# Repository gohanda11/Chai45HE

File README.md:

# Chai45HE

Chai45HE is a 40% Hall-effect keyboard based on the [HE60](https://github.com/peppapighs/HE60) project. This is a modified version that adapts the original 60% design to a compact 40% layout.

## Key Features

- 40% compact layout
- Hall-effect magnetic switches support
- Based on HE60's proven design and technology
- Custom PCB design files included

## ファームウェアの書き込み方法

1. [firmware.bin](firmware/firmware.bin) をダウンロードします。
2. 基板裏側の **BOOT** ボタンを長押ししながらUSBケーブルを接続し、Bootloader Modeに入ります。
3. [WebDFU](https://devanlai.github.io/webdfu/dfu-util/) にアクセスし、**DFU in FS mode** に接続します。
4. **Firmware Download** セクションでダウンロードした `firmware.bin` ファイルを選択します。
5. **Download** ボタンを押して書き込みを実行します。

## キー設定ガイド

### Tap-Holdの設定方法

Tap-Holdを使うと、短押し(Tap)と長押し(Hold)で異なるキーを割り当てることができます。

1. Remapで **Tap** に設定したいキーを配置します。
2. **Advanced Keys** から **Tap-Hold** を選択します。
3. **Hold** に設定したいキーを選択し、**Continue** を押します。
4. Hold用のキーを設定して **Done** で設定完了です。

### !@#$%などの記号キーの設定方法

Shiftキーとの組み合わせで入力される記号(!@#$%など)を単独のキーとして設定する方法です。

1. Remapで `1 2 3 4 5` を、`! @ # $ %` を入力したいキーに設定します。
2. **Advanced Keys** から **Dynamic Keystroke** を選択します。
3. 下の画像のようにShiftを割り当てます。

4. **Done** で設定完了です。

---

# HE60 (Original Project)

Below is the original README from the HE60 project, which this keyboard is based on.

---

# HE60

HE60 is a 60% Hall-effect keyboard PCB with 8kHz polling rate, a split spacebar and Tsangan layout support.

## Features

- Support for GH60 tray mount cases e.g., KBDfans Tofu60 Redux, and KBDfans Holy60.
- Support for gummy O-ring mount cases **if the USB-C port is not soldered** e.g., Bakeneko60, and SingaKBD Unikorn (required 10mm JST cable).
- [libhmk](https://github.com/peppapighs/libhmk) firmware.
- [hmkconf](https://hmk.prasertsuk.com) web-based configurator.

## Disclaimer

- The PCB requires standoffs to be mounted to the switch plate. The mounting points are **not compatible** with other available plates e.g., GEON Venom60 7U plate. HE60 v1 plate **is not compatible** with this PCB.

## Supported Layouts

## Fabrication

The following files are required:

- BOM (Bill of Materials): Contains the list of components required to build the PCB.
- Pick and Place: Contains the placement of the components on the PCB.
- Gerber: Contains the PCB design files for fabrication.

Note that the components in the BOM are all mounted on the bottom side of the PCB, and are based on the available components in JLCPCB at the time of writing. You may need to adjust the components based on your preference or availability. For the JST connector (labeled `JST_SH`), I used `WAFER-SH1.0-4PWB` offered by JLCPCB. **Make sure to deselect the USB-C port when choosing the components to solder if you are using the gummy O-ring version.**

You may change the Hall-effect sensors during the component selection based on your preference, and availability. Different sensors require different calibration values, which can be adjusted using the web-based configurator. Here are some options that I have used:

- GH39FKSW (Cheapest)
- MT9102ET
- SS39ET
- DRV5055A3
- OH49E-S (Discontinued)

The fabrication files above are available [here](https://github.com/peppapighs/HE60/releases).

## Build Guide

The following items are required to build the PCB:

- PCB
- Switch plate (DXF file available [here](/plate.dxf). You may need to use less flexible materials such as aluminum or FR4 to prevent the switch at the top right corner from popping out if you use the alternative backspace layout. If you would like to manufacture FR4 plate along with the PCB, you can find the GERBER file for the plate [here](https://github.com/peppapighs/HE60/releases).)
- Magnetic switches (e.g., GEON Raw HE, Gateron Magnetic Jade, Duhuk Core HE, etc.)
- Stabilizers (**Clip-in stabilizers are required for the gummy O-ring version**)
- M2 3.5mm standoffs x8
- M2 3mm flat head screws x16

1. Install the stabilizers to the PCB.

2. Attach the standoffs to the PCB using the M2 screws.

3. Install the switches to the plate. Assemble the plate and PCB together. Press the PCB against the plate to make sure the switches are seated properly. Screw the standoffs to the plate using the rest of the M2 screws.

4. Install the PCB into the case.

## Firmware

Head to [libhmk](https://github.com/peppapighs/libhmk/releases) for a pre-compiled firmware. The firmware can be flashed using DFU mode, which can be entered by holding the BOOT button before plugging in. You may need to install the DFU bootloader driver using Zadig. See [libhmk](https://github.com/peppapighs/libhmk) for more information for firmware flashing instructions.

## Acknowledgements

- Xelus from AEBoards for reviewing the PCB design and providing feedback.
- Keyboard Atelier community for supporting the project.

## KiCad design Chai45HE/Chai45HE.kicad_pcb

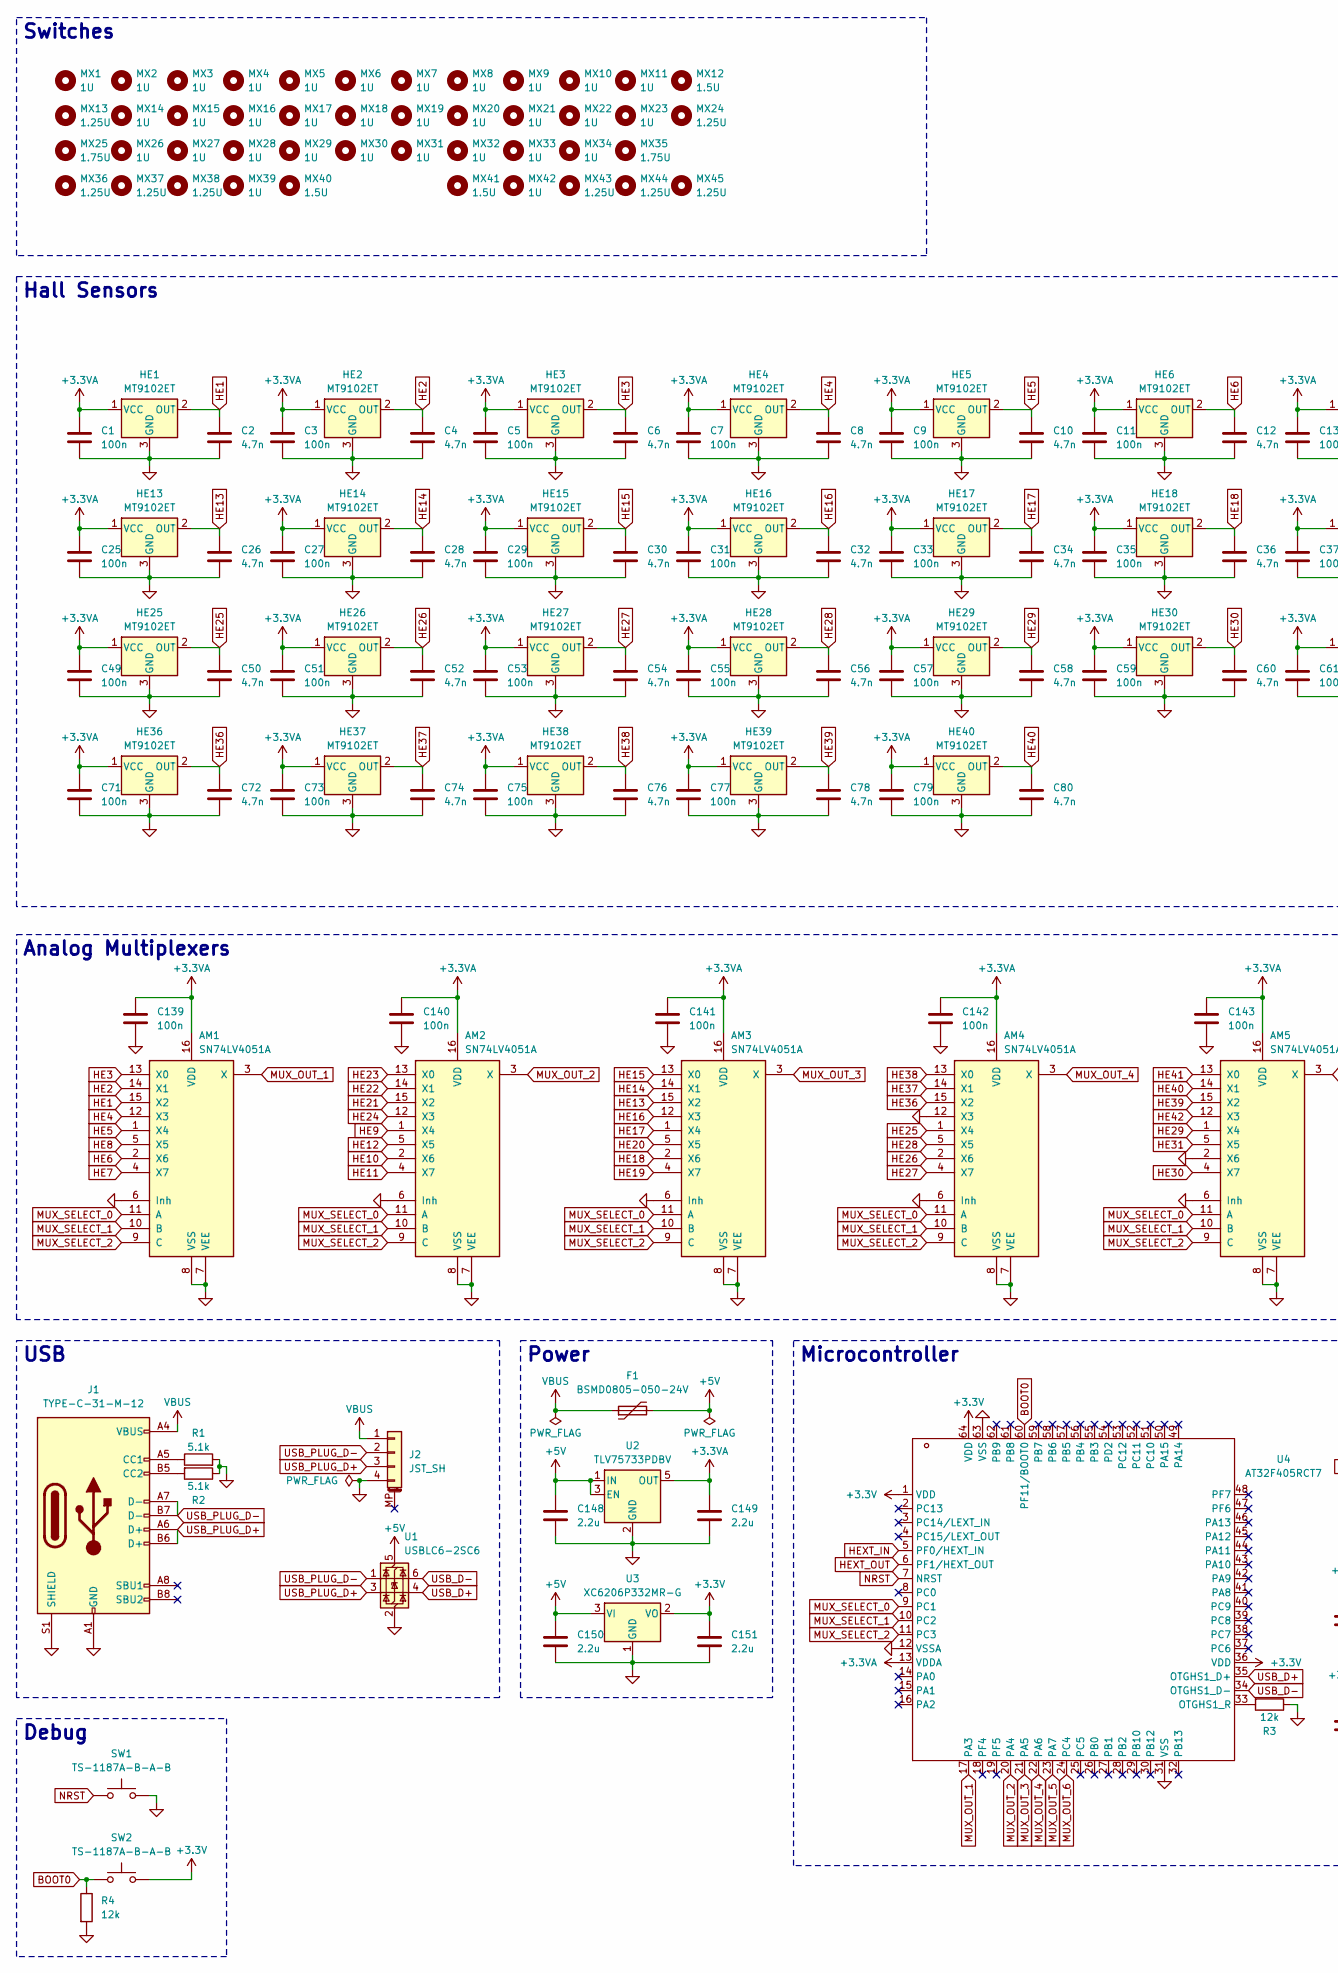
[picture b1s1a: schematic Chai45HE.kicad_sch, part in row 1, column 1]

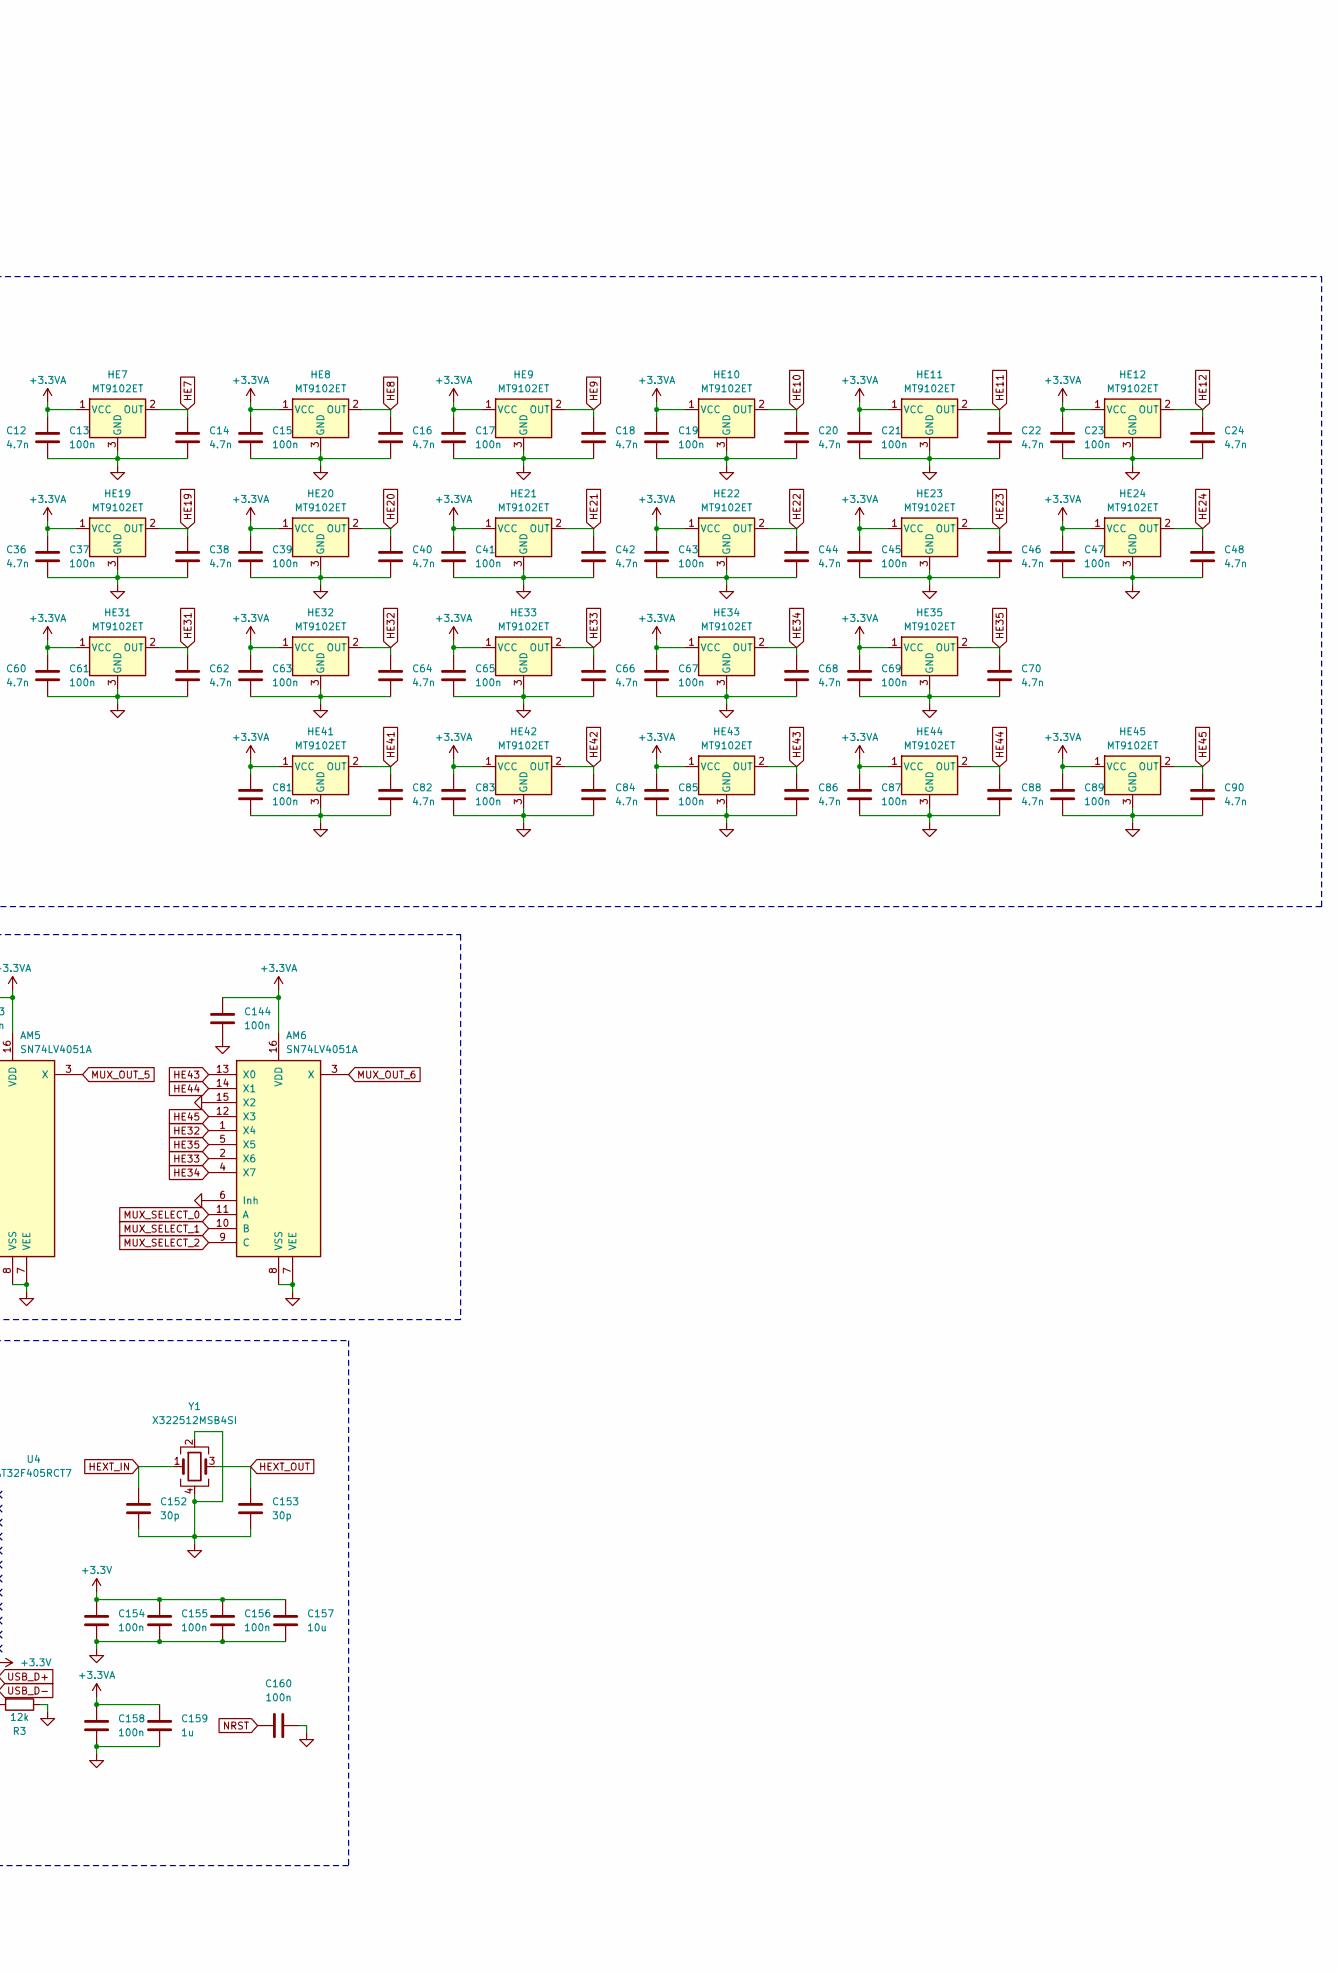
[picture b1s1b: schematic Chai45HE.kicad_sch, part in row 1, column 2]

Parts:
AM1, AM2, AM3, AM4, AM5, AM6: SN74LV4051A; TSSOP-16_4.4x5mm_P0.65mm
C1, C3, C5, C7, C9, C11, C13, C15, C17, C19, C21, C23, C25, C27, C29, C31, C33, C35, C37, C39, C41, C43, C45, C47, C49, C51, C53, C55, C57, C59, C61, C63, C65, C67, C69, C71, C73, C75, C77, C79, C81, C83, C85, C87, C89, C139, C140, C141, C142, C143, C144, C154, C155, C156, C158, C160: 100n; C_0402_1005Metric
C2, C4, C6, C8, C10, C12, C14, C16, C18, C20, C22, C24, C26, C28, C30, C32, C34, C36, C38, C40, C42, C44, C46, C48, C50, C52, C54, C56, C58, C60, C62, C64, C66, C68, C70, C72, C74, C76, C78, C80, C82, C84, C86, C88, C90: 4.7n; C_0402_1005Metric
C148, C149, C150, C151: 2.2u; C_0603_1608Metric
C152, C153: 30p; C_0603_1608Metric
C157: 10u; C_0603_1608Metric
C159: 1u; C_0603_1608Metric
F1: BSMD0805-050-24V; Fuse_0805_2012Metric
HE1, HE2, HE3, HE4, HE5, HE6, HE7, HE8, HE9, HE10, HE11, HE12, HE13, HE14, HE15, HE16, HE17, HE18, HE19, HE20, HE21, HE22, HE23, HE24, HE25, HE26, HE27, HE28, HE29, HE30, HE31, HE32, HE33, HE34, HE35, HE36, HE37, HE38, HE39, HE40, HE41, HE42, HE43, HE44, HE45: MT9102ET; SOT-23-3
J1: TYPE-C-31-M-12; USB_C_Receptacle_HRO_TYPE-C-31-M-12
J2: JST_SH; JST_SH_SM04B-SRSS-TB_1x04-1MP_P1.00mm_Horizontal
MX1, MX2, MX3, MX4, MX5, MX6, MX7, MX8, MX9, MX10, MX11, MX14, MX15, MX16, MX17, MX18, MX19, MX20, MX21, MX22, MX23, MX26, MX27, MX28, MX29, MX30, MX31, MX32, MX33, MX34, MX39, MX42: 1U; MX-1U
MX12, MX40, MX41: 1.5U; MX-1.5U
MX13, MX24, MX36, MX37, MX38, MX43, MX44, MX45: 1.25U; MX-1.25U
MX25, MX35: 1.75U; MX-1.75U
R1, R2: 5.1k; R_0402_1005Metric
R3, R4: 12k; R_0402_1005Metric
SW1, SW2: TS-1187A-B-A-B; SW_Push_1P1T_XKB_TS-1187A
U1: USBLC6-2SC6; SOT-23-6
U2: TLV75733PDBV; SOT-23-5
U3: XC6206P332MR-G; SOT-23-3
U4: AT32F405RCT7; LQFP-64_10x10mm_P0.5mm
Y1: X322512MSB4SI; Crystal_SMD_3225-4Pin_3.2x2.5mm

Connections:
+3.3V: C151.1, C154.1, C155.1, C156.1, C157.1, SW2.2, U3.2 (VO), U4.1 (VDD), U4.36 (VDD), U4.64 (VDD)
+3.3VA: AM1.16 (VDD), AM2.16 (VDD), AM3.16 (VDD), AM4.16 (VDD), AM5.16 (VDD), AM6.16 (VDD), C1.1, C3.1, C5.1, C7.1, C9.1, C11.1, C13.1, C15.1, C17.1, C19.1, C21.1, C23.1, C25.1, C27.1, C29.1, C31.1, C33.1, C35.1, C37.1, C39.1, C41.1, C43.1, C45.1, C47.1, C49.1, C51.1, C53.1, C55.1, C57.1, C59.1, C61.1, C63.1, C65.1, C67.1, C69.1, C71.1, C73.1, C75.1, C77.1, C79.1, C81.1, C83.1, C85.1, C87.1, C89.1, C139.1, C140.1, C141.1, C142.1, C143.1, C144.1, C149.1, C158.1, C159.1, HE1.1 (VCC), HE2.1 (VCC), HE3.1 (VCC), HE4.1 (VCC), HE5.1 (VCC), HE6.1 (VCC), HE7.1 (VCC), HE8.1 (VCC), HE9.1 (VCC), HE10.1 (VCC), HE11.1 (VCC), HE12.1 (VCC), HE13.1 (VCC), HE14.1 (VCC), HE15.1 (VCC), HE16.1 (VCC), HE17.1 (VCC), HE18.1 (VCC), HE19.1 (VCC), HE20.1 (VCC), HE21.1 (VCC), HE22.1 (VCC), HE23.1 (VCC), HE24.1 (VCC), HE25.1 (VCC), HE26.1 (VCC), HE27.1 (VCC), HE28.1 (VCC), HE29.1 (VCC), HE30.1 (VCC), HE31.1 (VCC), HE32.1 (VCC), HE33.1 (VCC), HE34.1 (VCC), HE35.1 (VCC), HE36.1 (VCC), HE37.1 (VCC), HE38.1 (VCC), HE39.1 (VCC), HE40.1 (VCC), HE41.1 (VCC), HE42.1 (VCC), HE43.1 (VCC), HE44.1 (VCC), HE45.1 (VCC), U2.5 (OUT), U4.13 (VDDA)
+5V: C148.1, C150.1, F1.2, U1.5 (VBUS), U2.1 (IN), U2.3 (EN), U3.3 (VI)
BOOT0: R4.1, SW2.1, U4.60 (PF11/BOOT0)
GND: AM1.6 (Inh), AM1.7 (VEE), AM1.8 (VSS), AM2.6 (Inh), AM2.7 (VEE), AM2.8 (VSS), AM3.6 (Inh), AM3.7 (VEE), AM3.8 (VSS), AM4.6 (Inh), AM4.7 (VEE), AM4.8 (VSS), AM4.12 (X3), AM5.2 (X6), AM5.6 (Inh), AM5.7 (VEE), AM5.8 (VSS), AM6.6 (Inh), AM6.7 (VEE), AM6.8 (VSS), AM6.15 (X2), C1.2, C2.2, C3.2, C4.2, C5.2, C6.2, C7.2, C8.2, C9.2, C10.2, C11.2, C12.2, C13.2, C14.2, C15.2, C16.2, C17.2, C18.2, C19.2, C20.2, C21.2, C22.2, C23.2, C24.2, C25.2, C26.2, C27.2, C28.2, C29.2, C30.2, C31.2, C32.2, C33.2, C34.2, C35.2, C36.2, C37.2, C38.2, C39.2, C40.2, C41.2, C42.2, C43.2, C44.2, C45.2, C46.2, C47.2, C48.2, C49.2, C50.2, C51.2, C52.2, C53.2, C54.2, C55.2, C56.2, C57.2, C58.2, C59.2, C60.2, C61.2, C62.2, C63.2, C64.2, C65.2, C66.2, C67.2, C68.2, C69.2, C70.2, C71.2, C72.2, C73.2, C74.2, C75.2, C76.2, C77.2, C78.2, C79.2, C80.2, C81.2, C82.2, C83.2, C84.2, C85.2, C86.2, C87.2, C88.2, C89.2, C90.2, C139.2, C140.2, C141.2, C142.2, C143.2, C144.2, C148.2, C149.2, C150.2, C151.2, C152.2, C153.2, C154.2, C155.2, C156.2, C157.2, C158.2, C159.2, C160.2, HE1.3 (GND), HE2.3 (GND), HE3.3 (GND), HE4.3 (GND), HE5.3 (GND), HE6.3 (GND), HE7.3 (GND), HE8.3 (GND), HE9.3 (GND), HE10.3 (GND), HE11.3 (GND), HE12.3 (GND), HE13.3 (GND), HE14.3 (GND), HE15.3 (GND), HE16.3 (GND), HE17.3 (GND), HE18.3 (GND), HE19.3 (GND), HE20.3 (GND), HE21.3 (GND), HE22.3 (GND), HE23.3 (GND), HE24.3 (GND), HE25.3 (GND), HE26.3 (GND), HE27.3 (GND), HE28.3 (GND), HE29.3 (GND), HE30.3 (GND), HE31.3 (GND), HE32.3 (GND), HE33.3 (GND), HE34.3 (GND), HE35.3 (GND), HE36.3 (GND), HE37.3 (GND), HE38.3 (GND), HE39.3 (GND), HE40.3 (GND), HE41.3 (GND), HE42.3 (GND), HE43.3 (GND), HE44.3 (GND), HE45.3 (GND), J1.A1 (GND), J1.A12 (GND), J1.B1 (GND), J1.B12 (GND), J1.S1 (SHIELD), J2.4, R1.2, R2.1, R3.1, R4.2, SW1.2, U1.2 (GND), U2.2 (GND), U3.1 (GND), U4.12 (VSSA), U4.31 (VSS), U4.63 (VSS), Y1.2, Y1.4
HE1: AM1.15 (X2), C2.1, HE1.2 (OUT)
HE2: AM1.14 (X1), C4.1, HE2.2 (OUT)
HE3: AM1.13 (X0), C6.1, HE3.2 (OUT)
HE4: AM1.12 (X3), C8.1, HE4.2 (OUT)
HE5: AM1.1 (X4), C10.1, HE5.2 (OUT)
HE6: AM1.2 (X6), C12.1, HE6.2 (OUT)
HE7: AM1.4 (X7), C14.1, HE7.2 (OUT)
HE8: AM1.5 (X5), C16.1, HE8.2 (OUT)
HE9: AM2.1 (X4), C18.1, HE9.2 (OUT)
HE10: AM2.2 (X6), C20.1, HE10.2 (OUT)
HE11: AM2.4 (X7), C22.1, HE11.2 (OUT)
HE12: AM2.5 (X5), C24.1, HE12.2 (OUT)
HE13: AM3.15 (X2), C26.1, HE13.2 (OUT)
HE14: AM3.14 (X1), C28.1, HE14.2 (OUT)
HE15: AM3.13 (X0), C30.1, HE15.2 (OUT)
HE16: AM3.12 (X3), C32.1, HE16.2 (OUT)
HE17: AM3.1 (X4), C34.1, HE17.2 (OUT)
HE18: AM3.2 (X6), C36.1, HE18.2 (OUT)
HE19: AM3.4 (X7), C38.1, HE19.2 (OUT)
HE20: AM3.5 (X5), C40.1, HE20.2 (OUT)
HE21: AM2.15 (X2), C42.1, HE21.2 (OUT)
HE22: AM2.14 (X1), C44.1, HE22.2 (OUT)
HE23: AM2.13 (X0), C46.1, HE23.2 (OUT)
HE24: AM2.12 (X3), C48.1, HE24.2 (OUT)
HE25: AM4.1 (X4), C50.1, HE25.2 (OUT)
HE26: AM4.2 (X6), C52.1, HE26.2 (OUT)
HE27: AM4.4 (X7), C54.1, HE27.2 (OUT)
HE28: AM4.5 (X5), C56.1, HE28.2 (OUT)
HE29: AM5.1 (X4), C58.1, HE29.2 (OUT)
HE30: AM5.4 (X7), C60.1, HE30.2 (OUT)
HE31: AM5.5 (X5), C62.1, HE31.2 (OUT)
HE32: AM6.1 (X4), C64.1, HE32.2 (OUT)
HE33: AM6.2 (X6), C66.1, HE33.2 (OUT)
HE34: AM6.4 (X7), C68.1, HE34.2 (OUT)
HE35: AM6.5 (X5), C70.1, HE35.2 (OUT)
HE36: AM4.15 (X2), C72.1, HE36.2 (OUT)
HE37: AM4.14 (X1), C74.1, HE37.2 (OUT)
HE38: AM4.13 (X0), C76.1, HE38.2 (OUT)
HE39: AM5.15 (X2), C78.1, HE39.2 (OUT)
HE40: AM5.14 (X1), C80.1, HE40.2 (OUT)
HE41: AM5.13 (X0), C82.1, HE41.2 (OUT)
HE42: AM5.12 (X3), C84.1, HE42.2 (OUT)
HE43: AM6.13 (X0), C86.1, HE43.2 (OUT)
HE44: AM6.14 (X1), C88.1, HE44.2 (OUT)
HE45: AM6.12 (X3), C90.1, HE45.2 (OUT)
HEXT_IN: C152.1, U4.5 (PF0/HEXT_IN), Y1.1
HEXT_OUT: C153.1, U4.6 (PF1/HEXT_OUT), Y1.3
MUX_OUT_1: AM1.3 (X), U4.17 (PA3)
MUX_OUT_2: AM2.3 (X), U4.20 (PA4)
MUX_OUT_3: AM3.3 (X), U4.21 (PA5)
MUX_OUT_4: AM4.3 (X), U4.22 (PA6)
MUX_OUT_5: AM5.3 (X), U4.23 (PA7)
MUX_OUT_6: AM6.3 (X), U4.24 (PC4)
MUX_SELECT_0: AM1.11 (A), AM2.11 (A), AM3.11 (A), AM4.11 (A), AM5.11 (A), AM6.11 (A), U4.9 (PC1)
MUX_SELECT_1: AM1.10 (B), AM2.10 (B), AM3.10 (B), AM4.10 (B), AM5.10 (B), AM6.10 (B), U4.10 (PC2)
MUX_SELECT_2: AM1.9 (C), AM2.9 (C), AM3.9 (C), AM4.9 (C), AM5.9 (C), AM6.9 (C), U4.11 (PC3)
NRST: C160.1, SW1.1, U4.7 (NRST)
unnamed: J1.A5 (CC1), R1.1
unnamed: J1.B5 (CC2), R2.2
unnamed: R3.2, U4.33 (OTGHS1_R)
USB_D+: U1.4 (I/O2), U4.35 (OTGHS1_D+)
USB_D-: U1.6 (I/O1), U4.34 (OTGHS1_D-)
USB_PLUG_D+: J1.A6 (D+), J1.B6 (D+), J2.3, U1.3 (I/O2)
USB_PLUG_D-: J1.A7 (D-), J1.B7 (D-), J2.2, U1.1 (I/O1)
VBUS: F1.1, J1.A4 (VBUS), J1.A9 (VBUS), J1.B4 (VBUS), J1.B9 (VBUS), J2.1

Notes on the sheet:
Hall Sensors
Switches
USB
Analog Multiplexers
Power
Debug
Microcontroller

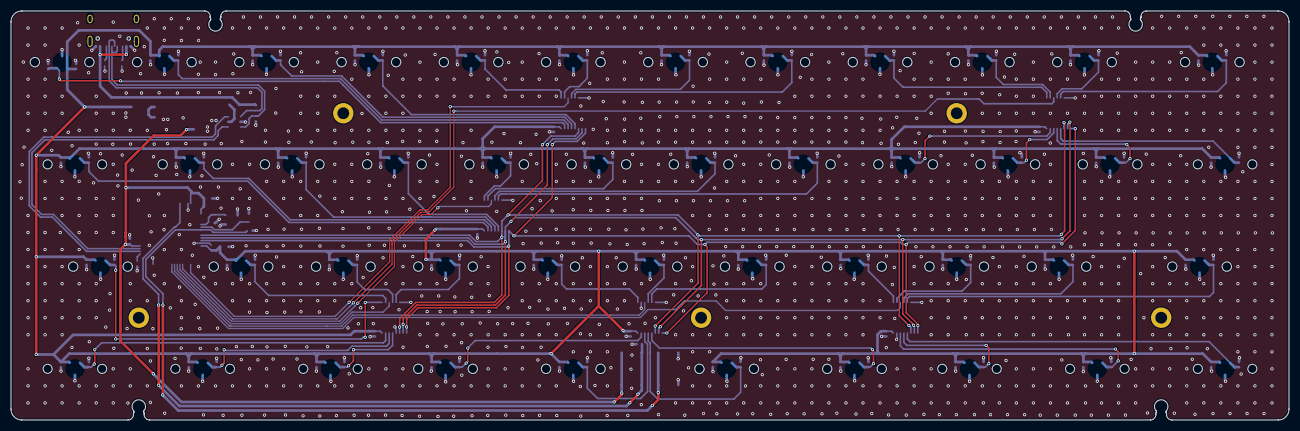
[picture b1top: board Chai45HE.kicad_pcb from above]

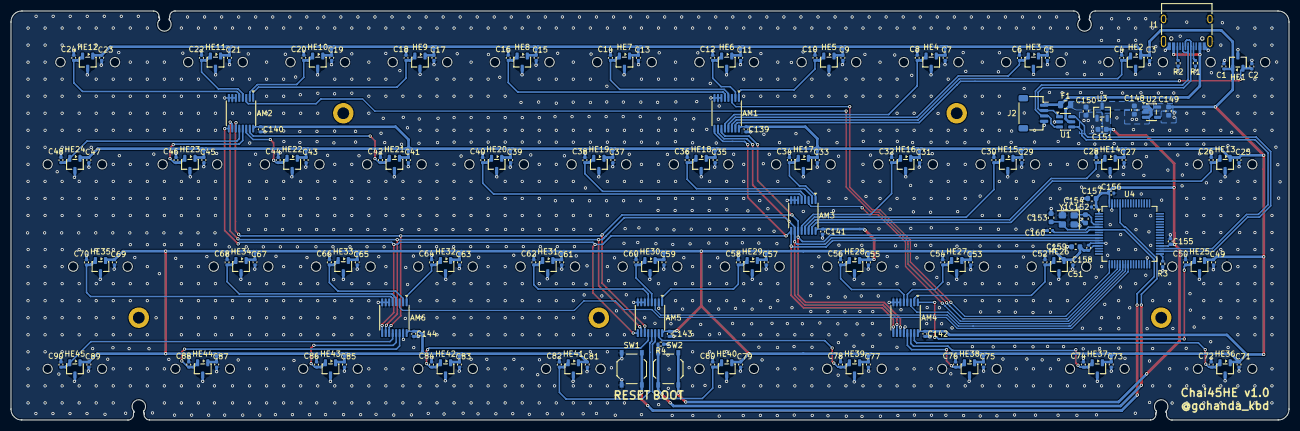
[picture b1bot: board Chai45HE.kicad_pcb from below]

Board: 2 copper layers, 238.1 x 76.2 mm, 219 parts (174 on the bottom side), 70 nets.

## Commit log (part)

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2026-02-20 READMEにファームウェアダウンロードの手順を追加
2026-02-20 gitignoreとファームウェアを追加
